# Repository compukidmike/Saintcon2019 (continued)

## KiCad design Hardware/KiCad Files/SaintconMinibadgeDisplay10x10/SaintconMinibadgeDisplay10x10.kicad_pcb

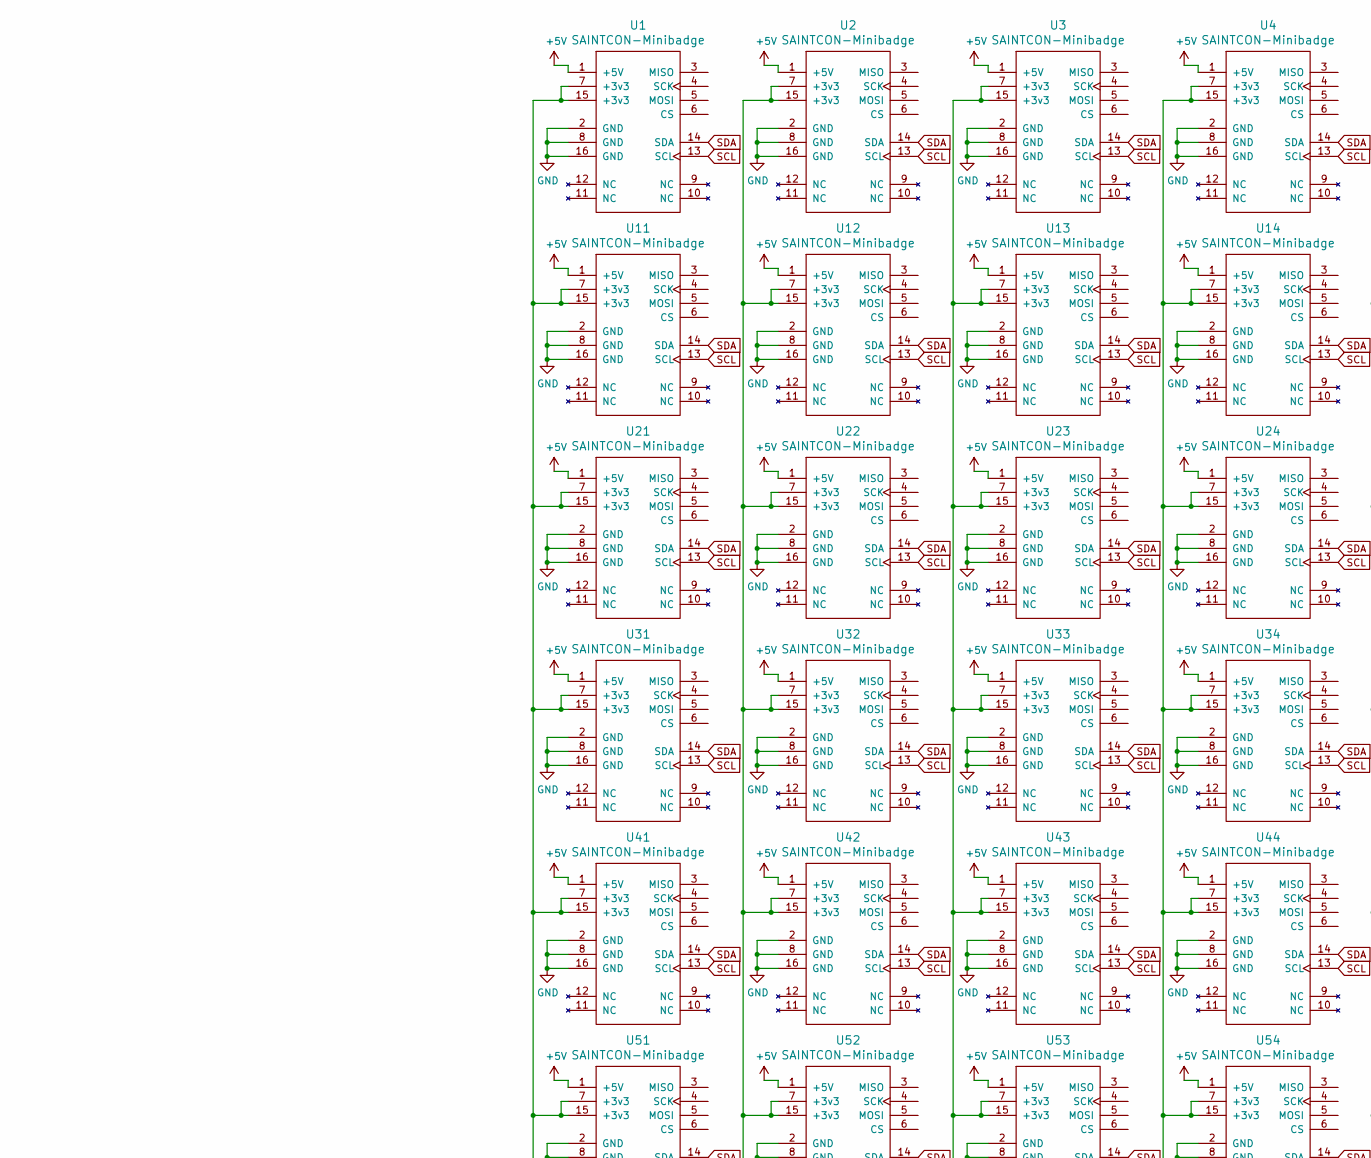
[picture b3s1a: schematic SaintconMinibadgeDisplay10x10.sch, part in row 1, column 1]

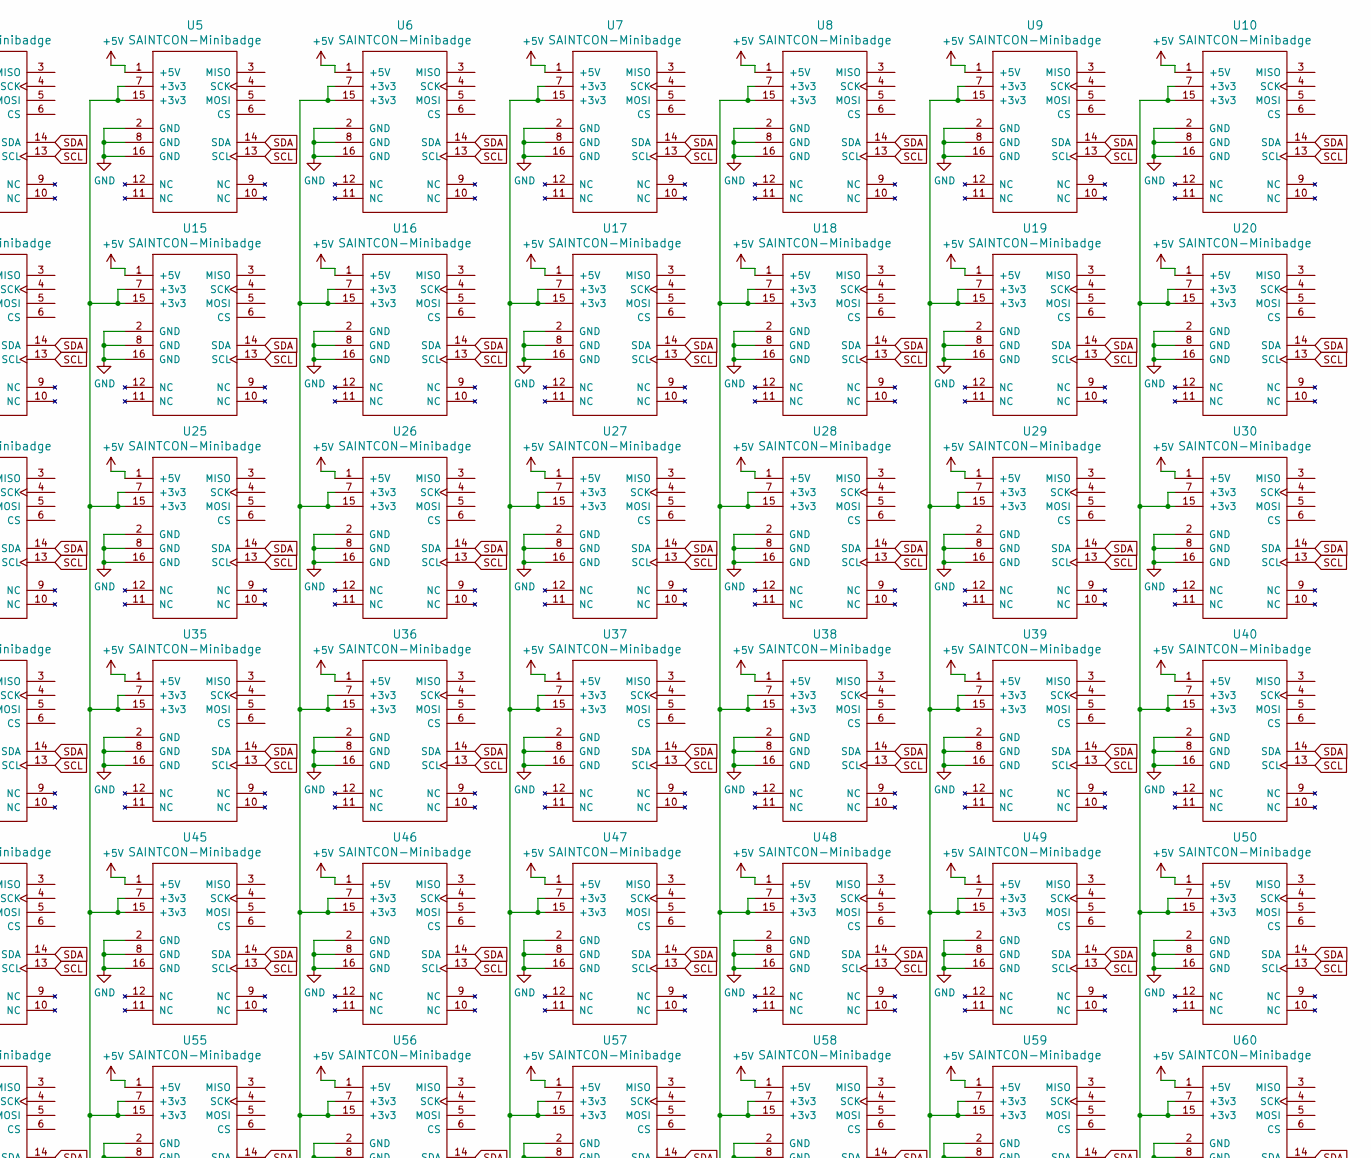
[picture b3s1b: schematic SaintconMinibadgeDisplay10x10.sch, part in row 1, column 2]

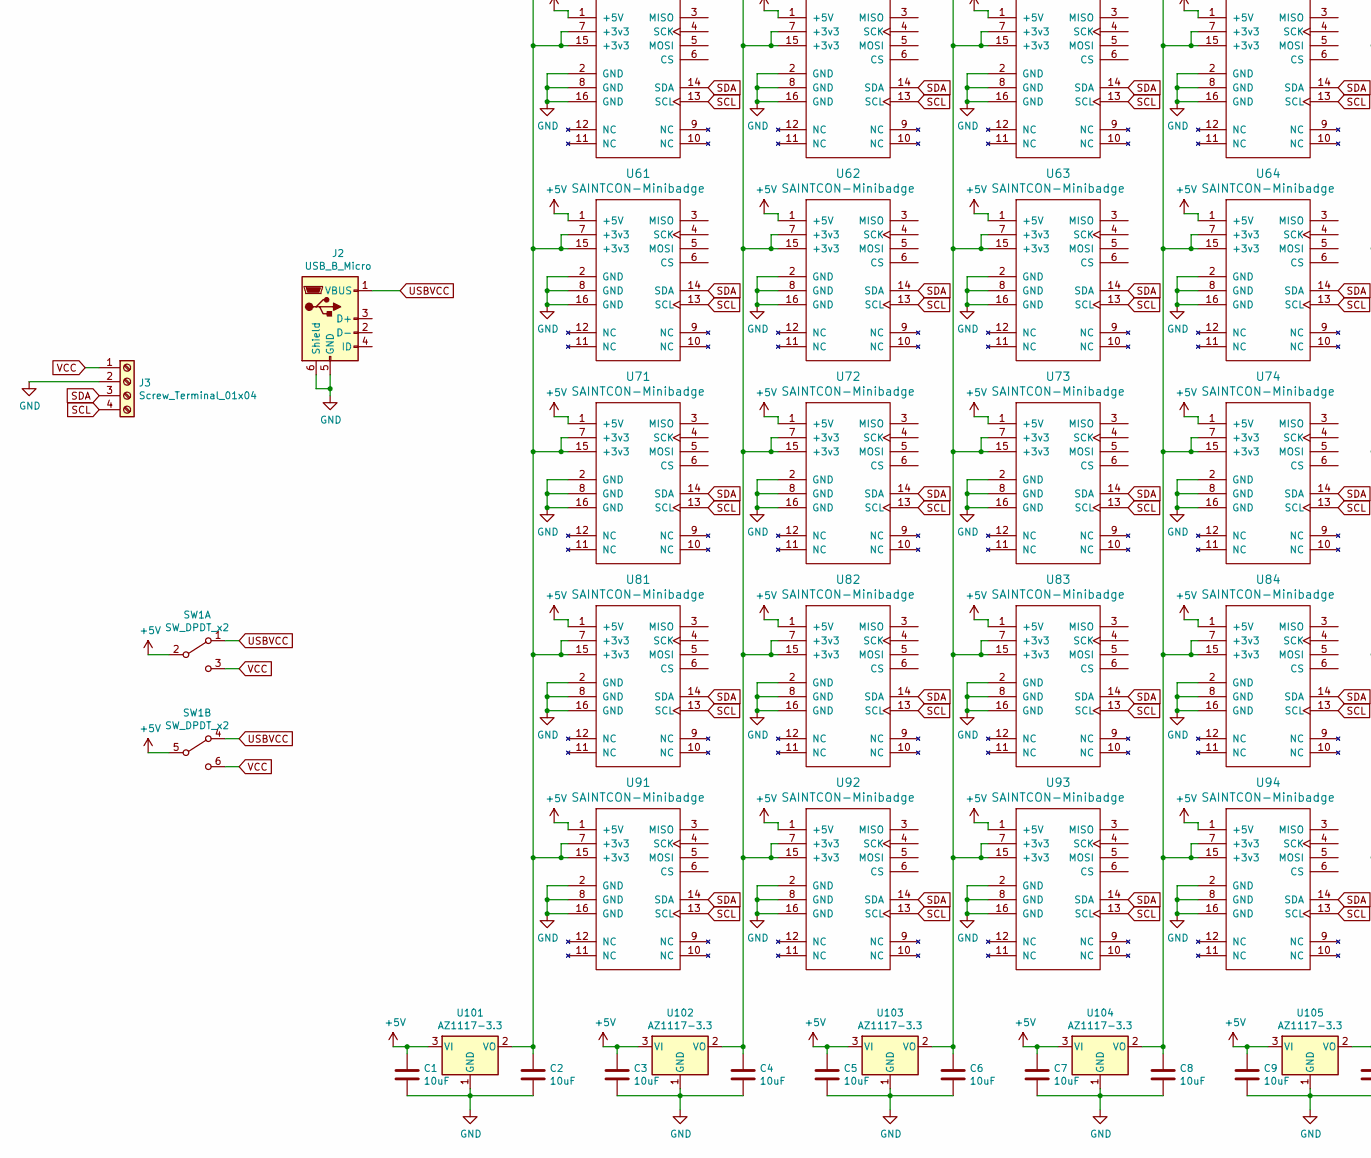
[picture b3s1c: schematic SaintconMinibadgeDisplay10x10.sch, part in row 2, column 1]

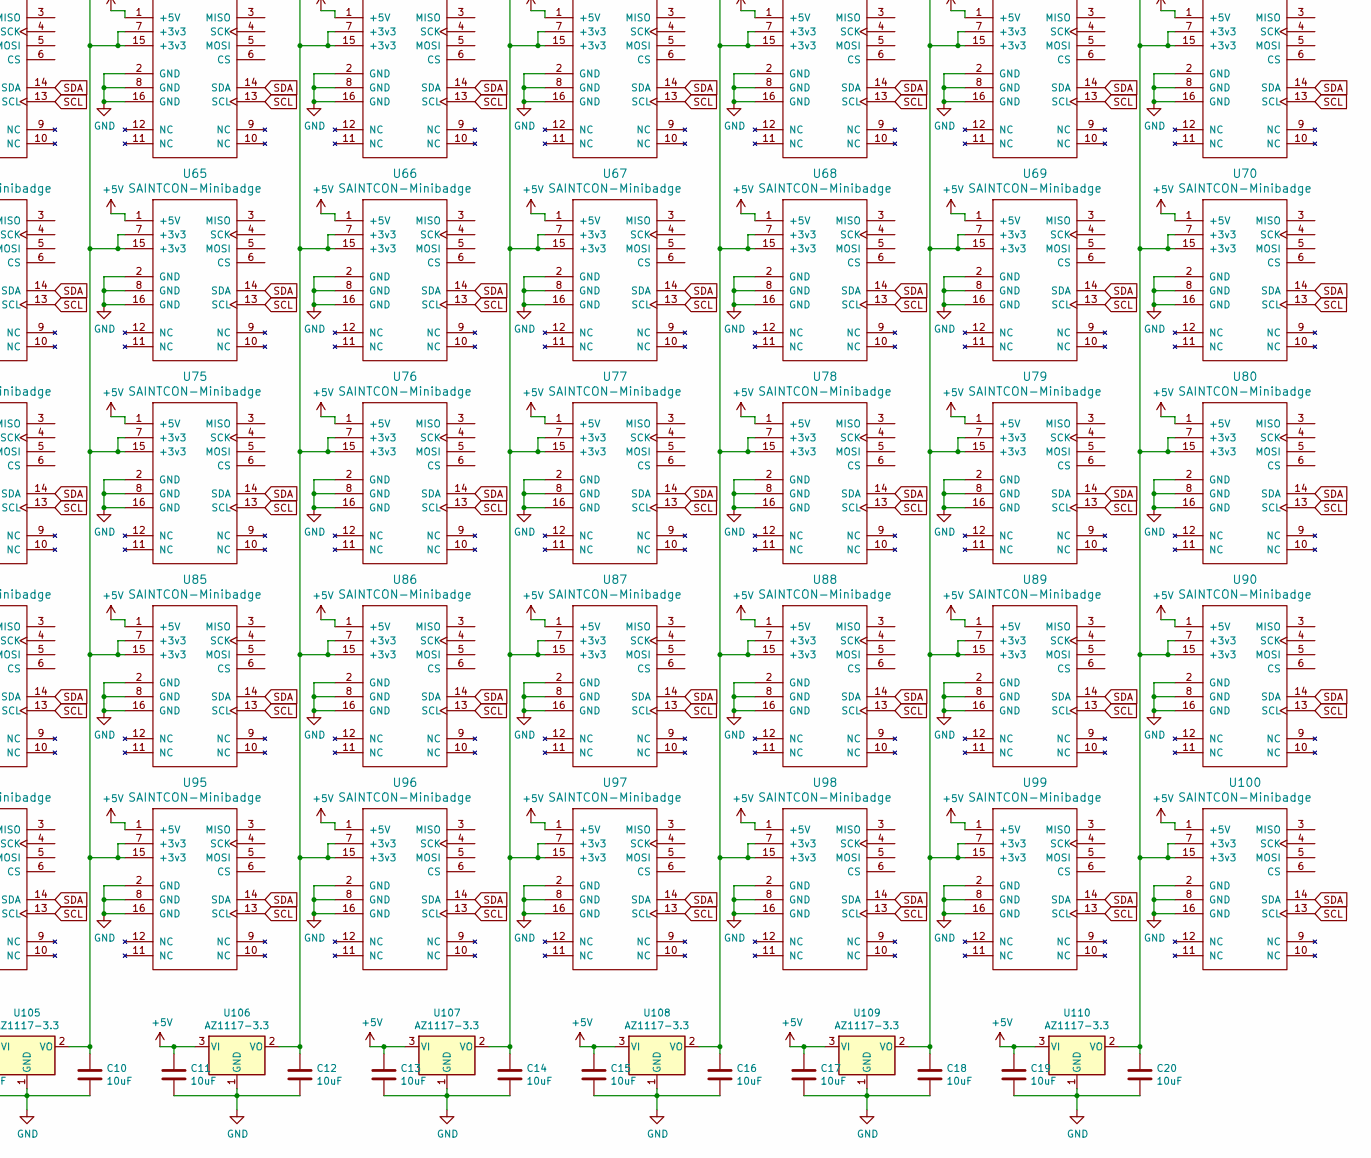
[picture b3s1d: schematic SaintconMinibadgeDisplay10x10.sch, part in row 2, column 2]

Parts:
C1, C2, C3, C4, C5, C6, C7, C8, C9, C10, C11, C12, C13, C14, C15, C16, C17, C18, C19, C20: 10uF; C_0805_HandSoldering
J2: USB_B_Micro; 10118192-0002LF
J3: Screw_Terminal_01x04; SCREWTERMINAL-3.5MM-4
SW1: SW_DPDT_x2; MFS201N-9-Z
U1, U2, U3, U4, U5, U6, U7, U8, U9, U10, U11, U12, U13, U14, U15, U16, U17, U18, U19, U20, U21, U22, U23, U24, U25, U26, U27, U28, U29, U30, U31, U32, U33, U34, U35, U36, U37, U38, U39, U40, U41, U42, U43, U44, U45, U46, U47, U48, U49, U50, U51, U52, U53, U54, U55, U56, U57, U58, U59, U60, U61, U62, U63, U64, U65, U66, U67, U68, U69, U70, U71, U72, U73, U74, U75, U76, U77, U78, U79, U80, U81, U82, U83, U84, U85, U86, U87, U88, U89, U90, U91, U92, U93, U94, U95, U96, U97, U98, U99, U100: SAINTCON-Minibadge; SAINTCON-Minibadge-Shiny
U101, U102, U103, U104, U105, U106, U107, U108, U109, U110: AZ1117-3.3; SOT-223-3_TabPin2

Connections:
+5V: C1.1, C3.1, C5.1, C7.1, C9.1, C11.1, C13.1, C15.1, C17.1, C19.1, SW1.2 (B), SW1.5 (B), U1.1 (+5V), U2.1 (+5V), U3.1 (+5V), U4.1 (+5V), U5.1 (+5V), U6.1 (+5V), U7.1 (+5V), U8.1 (+5V), U9.1 (+5V), U10.1 (+5V), U11.1 (+5V), U12.1 (+5V), U13.1 (+5V), U14.1 (+5V), U15.1 (+5V), U16.1 (+5V), U17.1 (+5V), U18.1 (+5V), U19.1 (+5V), U20.1 (+5V), U21.1 (+5V), U22.1 (+5V), U23.1 (+5V), U24.1 (+5V), U25.1 (+5V), U26.1 (+5V), U27.1 (+5V), U28.1 (+5V), U29.1 (+5V), U30.1 (+5V), U31.1 (+5V), U32.1 (+5V), U33.1 (+5V), U34.1 (+5V), U35.1 (+5V), U36.1 (+5V), U37.1 (+5V), U38.1 (+5V), U39.1 (+5V), U40.1 (+5V), U41.1 (+5V), U42.1 (+5V), U43.1 (+5V), U44.1 (+5V), U45.1 (+5V), U46.1 (+5V), U47.1 (+5V), U48.1 (+5V), U49.1 (+5V), U50.1 (+5V), U51.1 (+5V), U52.1 (+5V), U53.1 (+5V), U54.1 (+5V), U55.1 (+5V), U56.1 (+5V), U57.1 (+5V), U58.1 (+5V), U59.1 (+5V), U60.1 (+5V), U61.1 (+5V), U62.1 (+5V), U63.1 (+5V), U64.1 (+5V), U65.1 (+5V), U66.1 (+5V), U67.1 (+5V), U68.1 (+5V), U69.1 (+5V), U70.1 (+5V), U71.1 (+5V), U72.1 (+5V), U73.1 (+5V), U74.1 (+5V), U75.1 (+5V), U76.1 (+5V), U77.1 (+5V), U78.1 (+5V), U79.1 (+5V), U80.1 (+5V), U81.1 (+5V), U82.1 (+5V), U83.1 (+5V), U84.1 (+5V), U85.1 (+5V), U86.1 (+5V), U87.1 (+5V), U88.1 (+5V), U89.1 (+5V), U90.1 (+5V), U91.1 (+5V), U92.1 (+5V), U93.1 (+5V), U94.1 (+5V), U95.1 (+5V), U96.1 (+5V), U97.1 (+5V), U98.1 (+5V), U99.1 (+5V), U100.1 (+5V), U101.3 (VI), U102.3 (VI), U103.3 (VI), U104.3 (VI), U105.3 (VI), U106.3 (VI), U107.3 (VI), U108.3 (VI), U109.3 (VI), U110.3 (VI)
GND: C1.2, C2.2, C3.2, C4.2, C5.2, C6.2, C7.2, C8.2, C9.2, C10.2, C11.2, C12.2, C13.2, C14.2, C15.2, C16.2, C17.2, C18.2, C19.2, C20.2, J2.5 (GND), J2.6 (Shield), J3.2, U1.2 (GND), U1.8 (GND), U1.16 (GND), U2.2 (GND), U2.8 (GND), U2.16 (GND), U3.2 (GND), U3.8 (GND), U3.16 (GND), U4.2 (GND), U4.8 (GND), U4.16 (GND), U5.2 (GND), U5.8 (GND), U5.16 (GND), U6.2 (GND), U6.8 (GND), U6.16 (GND), U7.2 (GND), U7.8 (GND), U7.16 (GND), U8.2 (GND), U8.8 (GND), U8.16 (GND), U9.2 (GND), U9.8 (GND), U9.16 (GND), U10.2 (GND), U10.8 (GND), U10.16 (GND), U11.2 (GND), U11.8 (GND), U11.16 (GND), U12.2 (GND), U12.8 (GND), U12.16 (GND), U13.2 (GND), U13.8 (GND), U13.16 (GND), U14.2 (GND), U14.8 (GND), U14.16 (GND), U15.2 (GND), U15.8 (GND), U15.16 (GND), U16.2 (GND), U16.8 (GND), U16.16 (GND), U17.2 (GND), U17.8 (GND), U17.16 (GND), U18.2 (GND), U18.8 (GND), U18.16 (GND), U19.2 (GND), U19.8 (GND), U19.16 (GND), U20.2 (GND), U20.8 (GND), U20.16 (GND), U21.2 (GND), U21.8 (GND), U21.16 (GND), U22.2 (GND), U22.8 (GND), U22.16 (GND), U23.2 (GND), U23.8 (GND), U23.16 (GND), U24.2 (GND), U24.8 (GND), U24.16 (GND), U25.2 (GND), U25.8 (GND), U25.16 (GND), U26.2 (GND), U26.8 (GND), U26.16 (GND), U27.2 (GND), U27.8 (GND), U27.16 (GND), U28.2 (GND), U28.8 (GND), U28.16 (GND), U29.2 (GND), U29.8 (GND), U29.16 (GND), U30.2 (GND), U30.8 (GND), U30.16 (GND), U31.2 (GND), U31.8 (GND), U31.16 (GND), U32.2 (GND), U32.8 (GND), U32.16 (GND), U33.2 (GND), U33.8 (GND), U33.16 (GND), U34.2 (GND), U34.8 (GND), U34.16 (GND), U35.2 (GND), U35.8 (GND), U35.16 (GND), U36.2 (GND), U36.8 (GND), U36.16 (GND), U37.2 (GND), U37.8 (GND), U37.16 (GND), U38.2 (GND), U38.8 (GND), U38.16 (GND), U39.2 (GND), U39.8 (GND), U39.16 (GND), U40.2 (GND), U40.8 (GND), U40.16 (GND), U41.2 (GND), U41.8 (GND), U41.16 (GND), U42.2 (GND), U42.8 (GND), U42.16 (GND), U43.2 (GND), U43.8 (GND), U43.16 (GND), U44.2 (GND), U44.8 (GND), U44.16 (GND), U45.2 (GND), U45.8 (GND), U45.16 (GND), U46.2 (GND), U46.8 (GND), U46.16 (GND), U47.2 (GND), U47.8 (GND), U47.16 (GND), U48.2 (GND), U48.8 (GND), U48.16 (GND), U49.2 (GND), U49.8 (GND), U49.16 (GND), U50.2 (GND), U50.8 (GND), U50.16 (GND), U51.2 (GND), U51.8 (GND), U51.16 (GND), U52.2 (GND), U52.8 (GND), U52.16 (GND), U53.2 (GND), U53.8 (GND), U53.16 (GND), U54.2 (GND), U54.8 (GND), U54.16 (GND), U55.2 (GND), U55.8 (GND), U55.16 (GND), U56.2 (GND), U56.8 (GND), U56.16 (GND), U57.2 (GND), U57.8 (GND), U57.16 (GND), U58.2 (GND), U58.8 (GND), U58.16 (GND), U59.2 (GND), U59.8 (GND), U59.16 (GND), U60.2 (GND), U60.8 (GND), U60.16 (GND), U61.2 (GND), U61.8 (GND), U61.16 (GND), U62.2 (GND), U62.8 (GND), U62.16 (GND), U63.2 (GND), U63.8 (GND), U63.16 (GND), U64.2 (GND), U64.8 (GND), U64.16 (GND), U65.2 (GND), U65.8 (GND), U65.16 (GND), U66.2 (GND), U66.8 (GND), U66.16 (GND), U67.2 (GND), U67.8 (GND), U67.16 (GND), U68.2 (GND), U68.8 (GND), U68.16 (GND), U69.2 (GND), U69.8 (GND), U69.16 (GND), U70.2 (GND), U70.8 (GND), U70.16 (GND), U71.2 (GND), U71.8 (GND), U71.16 (GND), U72.2 (GND), U72.8 (GND), U72.16 (GND), U73.2 (GND), U73.8 (GND), U73.16 (GND), U74.2 (GND), U74.8 (GND), U74.16 (GND), U75.2 (GND), U75.8 (GND), U75.16 (GND), U76.2 (GND), U76.8 (GND), U76.16 (GND), U77.2 (GND), U77.8 (GND), U77.16 (GND), U78.2 (GND), U78.8 (GND), U78.16 (GND), U79.2 (GND), U79.8 (GND), U79.16 (GND), U80.2 (GND), U80.8 (GND), U80.16 (GND), U81.2 (GND), U81.8 (GND), U81.16 (GND), U82.2 (GND), U82.8 (GND), U82.16 (GND), U83.2 (GND), U83.8 (GND), U83.16 (GND), U84.2 (GND), U84.8 (GND), U84.16 (GND), U85.2 (GND), U85.8 (GND), U85.16 (GND), U86.2 (GND), U86.8 (GND), U86.16 (GND), U87.2 (GND), U87.8 (GND), U87.16 (GND), U88.2 (GND), U88.8 (GND), U88.16 (GND), U89.2 (GND), U89.8 (GND), U89.16 (GND), U90.2 (GND), U90.8 (GND), U90.16 (GND), U91.2 (GND), U91.8 (GND), U91.16 (GND), U92.2 (GND), U92.8 (GND), U92.16 (GND), U93.2 (GND), U93.8 (GND), U93.16 (GND), U94.2 (GND), U94.8 (GND), U94.16 (GND), U95.2 (GND), U95.8 (GND), U95.16 (GND), U96.2 (GND), U96.8 (GND), U96.16 (GND), U97.2 (GND), U97.8 (GND), U97.16 (GND), U98.2 (GND), U98.8 (GND), U98.16 (GND), U99.2 (GND), U99.8 (GND), U99.16 (GND), U100.2 (GND), U100.8 (GND), U100.16 (GND), U101.1 (GND), U102.1 (GND), U103.1 (GND), U104.1 (GND), U105.1 (GND), U106.1 (GND), U107.1 (GND), U108.1 (GND), U109.1 (GND), U110.1 (GND)
unnamed: C2.1, U1.7 (+3v3), U1.15 (+3v3), U11.7 (+3v3), U11.15 (+3v3), U21.7 (+3v3), U21.15 (+3v3), U31.7 (+3v3), U31.15 (+3v3), U41.7 (+3v3), U41.15 (+3v3), U51.7 (+3v3), U51.15 (+3v3), U61.7 (+3v3), U61.15 (+3v3), U71.7 (+3v3), U71.15 (+3v3), U81.7 (+3v3), U81.15 (+3v3), U91.7 (+3v3), U91.15 (+3v3), U101.2 (VO)
unnamed: C4.1, U2.7 (+3v3), U2.15 (+3v3), U12.7 (+3v3), U12.15 (+3v3), U22.7 (+3v3), U22.15 (+3v3), U32.7 (+3v3), U32.15 (+3v3), U42.7 (+3v3), U42.15 (+3v3), U52.7 (+3v3), U52.15 (+3v3), U62.7 (+3v3), U62.15 (+3v3), U72.7 (+3v3), U72.15 (+3v3), U82.7 (+3v3), U82.15 (+3v3), U92.7 (+3v3), U92.15 (+3v3), U102.2 (VO)
unnamed: C6.1, U3.7 (+3v3), U3.15 (+3v3), U13.7 (+3v3), U13.15 (+3v3), U23.7 (+3v3), U23.15 (+3v3), U33.7 (+3v3), U33.15 (+3v3), U43.7 (+3v3), U43.15 (+3v3), U53.7 (+3v3), U53.15 (+3v3), U63.7 (+3v3), U63.15 (+3v3), U73.7 (+3v3), U73.15 (+3v3), U83.7 (+3v3), U83.15 (+3v3), U93.7 (+3v3), U93.15 (+3v3), U103.2 (VO)
unnamed: C8.1, U4.7 (+3v3), U4.15 (+3v3), U14.7 (+3v3), U14.15 (+3v3), U24.7 (+3v3), U24.15 (+3v3), U34.7 (+3v3), U34.15 (+3v3), U44.7 (+3v3), U44.15 (+3v3), U54.7 (+3v3), U54.15 (+3v3), U64.7 (+3v3), U64.15 (+3v3), U74.7 (+3v3), U74.15 (+3v3), U84.7 (+3v3), U84.15 (+3v3), U94.7 (+3v3), U94.15 (+3v3), U104.2 (VO)
unnamed: C10.1, U5.7 (+3v3), U5.15 (+3v3), U15.7 (+3v3), U15.15 (+3v3), U25.7 (+3v3), U25.15 (+3v3), U35.7 (+3v3), U35.15 (+3v3), U45.7 (+3v3), U45.15 (+3v3), U55.7 (+3v3), U55.15 (+3v3), U65.7 (+3v3), U65.15 (+3v3), U75.7 (+3v3), U75.15 (+3v3), U85.7 (+3v3), U85.15 (+3v3), U95.7 (+3v3), U95.15 (+3v3), U105.2 (VO)
unnamed: C12.1, U6.7 (+3v3), U6.15 (+3v3), U16.7 (+3v3), U16.15 (+3v3), U26.7 (+3v3), U26.15 (+3v3), U36.7 (+3v3), U36.15 (+3v3), U46.7 (+3v3), U46.15 (+3v3), U56.7 (+3v3), U56.15 (+3v3), U66.7 (+3v3), U66.15 (+3v3), U76.7 (+3v3), U76.15 (+3v3), U86.7 (+3v3), U86.15 (+3v3), U96.7 (+3v3), U96.15 (+3v3), U106.2 (VO)
unnamed: C14.1, U7.7 (+3v3), U7.15 (+3v3), U17.7 (+3v3), U17.15 (+3v3), U27.7 (+3v3), U27.15 (+3v3), U37.7 (+3v3), U37.15 (+3v3), U47.7 (+3v3), U47.15 (+3v3), U57.7 (+3v3), U57.15 (+3v3), U67.7 (+3v3), U67.15 (+3v3), U77.7 (+3v3), U77.15 (+3v3), U87.7 (+3v3), U87.15 (+3v3), U97.7 (+3v3), U97.15 (+3v3), U107.2 (VO)
unnamed: C16.1, U8.7 (+3v3), U8.15 (+3v3), U18.7 (+3v3), U18.15 (+3v3), U28.7 (+3v3), U28.15 (+3v3), U38.7 (+3v3), U38.15 (+3v3), U48.7 (+3v3), U48.15 (+3v3), U58.7 (+3v3), U58.15 (+3v3), U68.7 (+3v3), U68.15 (+3v3), U78.7 (+3v3), U78.15 (+3v3), U88.7 (+3v3), U88.15 (+3v3), U98.7 (+3v3), U98.15 (+3v3), U108.2 (VO)
unnamed: C18.1, U9.7 (+3v3), U9.15 (+3v3), U19.7 (+3v3), U19.15 (+3v3), U29.7 (+3v3), U29.15 (+3v3), U39.7 (+3v3), U39.15 (+3v3), U49.7 (+3v3), U49.15 (+3v3), U59.7 (+3v3), U59.15 (+3v3), U69.7 (+3v3), U69.15 (+3v3), U79.7 (+3v3), U79.15 (+3v3), U89.7 (+3v3), U89.15 (+3v3), U99.7 (+3v3), U99.15 (+3v3), U109.2 (VO)
unnamed: C20.1, U10.7 (+3v3), U10.15 (+3v3), U20.7 (+3v3), U20.15 (+3v3), U30.7 (+3v3), U30.15 (+3v3), U40.7 (+3v3), U40.15 (+3v3), U50.7 (+3v3), U50.15 (+3v3), U60.7 (+3v3), U60.15 (+3v3), U70.7 (+3v3), U70.15 (+3v3), U80.7 (+3v3), U80.15 (+3v3), U90.7 (+3v3), U90.15 (+3v3), U100.7 (+3v3), U100.15 (+3v3), U110.2 (VO)
SCL: J3.4, U1.13 (SCL), U2.13 (SCL), U3.13 (SCL), U4.13 (SCL), U5.13 (SCL), U6.13 (SCL), U7.13 (SCL), U8.13 (SCL), U9.13 (SCL), U10.13 (SCL), U11.13 (SCL), U12.13 (SCL), U13.13 (SCL), U14.13 (SCL), U15.13 (SCL), U16.13 (SCL), U17.13 (SCL), U18.13 (SCL), U19.13 (SCL), U20.13 (SCL), U21.13 (SCL), U22.13 (SCL), U23.13 (SCL), U24.13 (SCL), U25.13 (SCL), U26.13 (SCL), U27.13 (SCL), U28.13 (SCL), U29.13 (SCL), U30.13 (SCL), U31.13 (SCL), U32.13 (SCL), U33.13 (SCL), U34.13 (SCL), U35.13 (SCL), U36.13 (SCL), U37.13 (SCL), U38.13 (SCL), U39.13 (SCL), U40.13 (SCL), U41.13 (SCL), U42.13 (SCL), U43.13 (SCL), U44.13 (SCL), U45.13 (SCL), U46.13 (SCL), U47.13 (SCL), U48.13 (SCL), U49.13 (SCL), U50.13 (SCL), U51.13 (SCL), U52.13 (SCL), U53.13 (SCL), U54.13 (SCL), U55.13 (SCL), U56.13 (SCL), U57.13 (SCL), U58.13 (SCL), U59.13 (SCL), U60.13 (SCL), U61.13 (SCL), U62.13 (SCL), U63.13 (SCL), U64.13 (SCL), U65.13 (SCL), U66.13 (SCL), U67.13 (SCL), U68.13 (SCL), U69.13 (SCL), U70.13 (SCL), U71.13 (SCL), U72.13 (SCL), U73.13 (SCL), U74.13 (SCL), U75.13 (SCL), U76.13 (SCL), U77.13 (SCL), U78.13 (SCL), U79.13 (SCL), U80.13 (SCL), U81.13 (SCL), U82.13 (SCL), U83.13 (SCL), U84.13 (SCL), U85.13 (SCL), U86.13 (SCL), U87.13 (SCL), U88.13 (SCL), U89.13 (SCL), U90.13 (SCL), U91.13 (SCL), U92.13 (SCL), U93.13 (SCL), U94.13 (SCL), U95.13 (SCL), U96.13 (SCL), U97.13 (SCL), U98.13 (SCL), U99.13 (SCL), U100.13 (SCL)
SDA: J3.3, U1.14 (SDA), U2.14 (SDA), U3.14 (SDA), U4.14 (SDA), U5.14 (SDA), U6.14 (SDA), U7.14 (SDA), U8.14 (SDA), U9.14 (SDA), U10.14 (SDA), U11.14 (SDA), U12.14 (SDA), U13.14 (SDA), U14.14 (SDA), U15.14 (SDA), U16.14 (SDA), U17.14 (SDA), U18.14 (SDA), U19.14 (SDA), U20.14 (SDA), U21.14 (SDA), U22.14 (SDA), U23.14 (SDA), U24.14 (SDA), U25.14 (SDA), U26.14 (SDA), U27.14 (SDA), U28.14 (SDA), U29.14 (SDA), U30.14 (SDA), U31.14 (SDA), U32.14 (SDA), U33.14 (SDA), U34.14 (SDA), U35.14 (SDA), U36.14 (SDA), U37.14 (SDA), U38.14 (SDA), U39.14 (SDA), U40.14 (SDA), U41.14 (SDA), U42.14 (SDA), U43.14 (SDA), U44.14 (SDA), U45.14 (SDA), U46.14 (SDA), U47.14 (SDA), U48.14 (SDA), U49.14 (SDA), U50.14 (SDA), U51.14 (SDA), U52.14 (SDA), U53.14 (SDA), U54.14 (SDA), U55.14 (SDA), U56.14 (SDA), U57.14 (SDA), U58.14 (SDA), U59.14 (SDA), U60.14 (SDA), U61.14 (SDA), U62.14 (SDA), U63.14 (SDA), U64.14 (SDA), U65.14 (SDA), U66.14 (SDA), U67.14 (SDA), U68.14 (SDA), U69.14 (SDA), U70.14 (SDA), U71.14 (SDA), U72.14 (SDA), U73.14 (SDA), U74.14 (SDA), U75.14 (SDA), U76.14 (SDA), U77.14 (SDA), U78.14 (SDA), U79.14 (SDA), U80.14 (SDA), U81.14 (SDA), U82.14 (SDA), U83.14 (SDA), U84.14 (SDA), U85.14 (SDA), U86.14 (SDA), U87.14 (SDA), U88.14 (SDA), U89.14 (SDA), U90.14 (SDA), U91.14 (SDA), U92.14 (SDA), U93.14 (SDA), U94.14 (SDA), U95.14 (SDA), U96.14 (SDA), U97.14 (SDA), U98.14 (SDA), U99.14 (SDA), U100.14 (SDA)
USBVCC: J2.1 (VBUS), SW1.1 (A), SW1.4 (A)
VCC: J3.1, SW1.3 (C), SW1.6 (C)

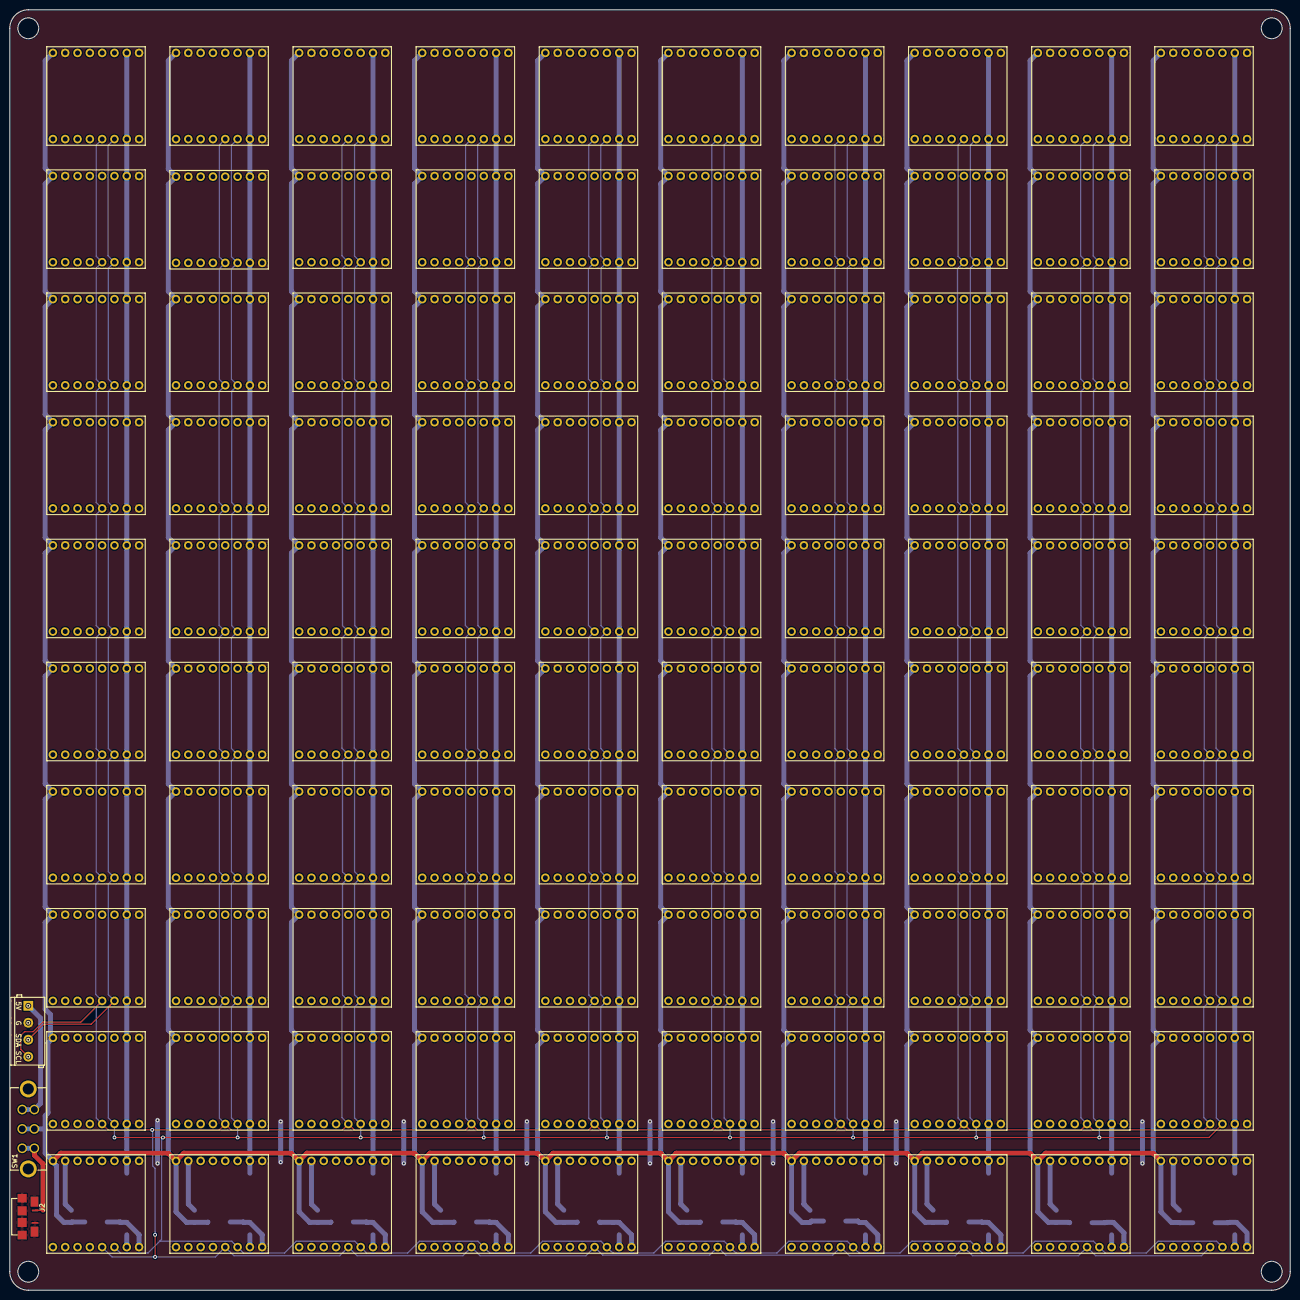
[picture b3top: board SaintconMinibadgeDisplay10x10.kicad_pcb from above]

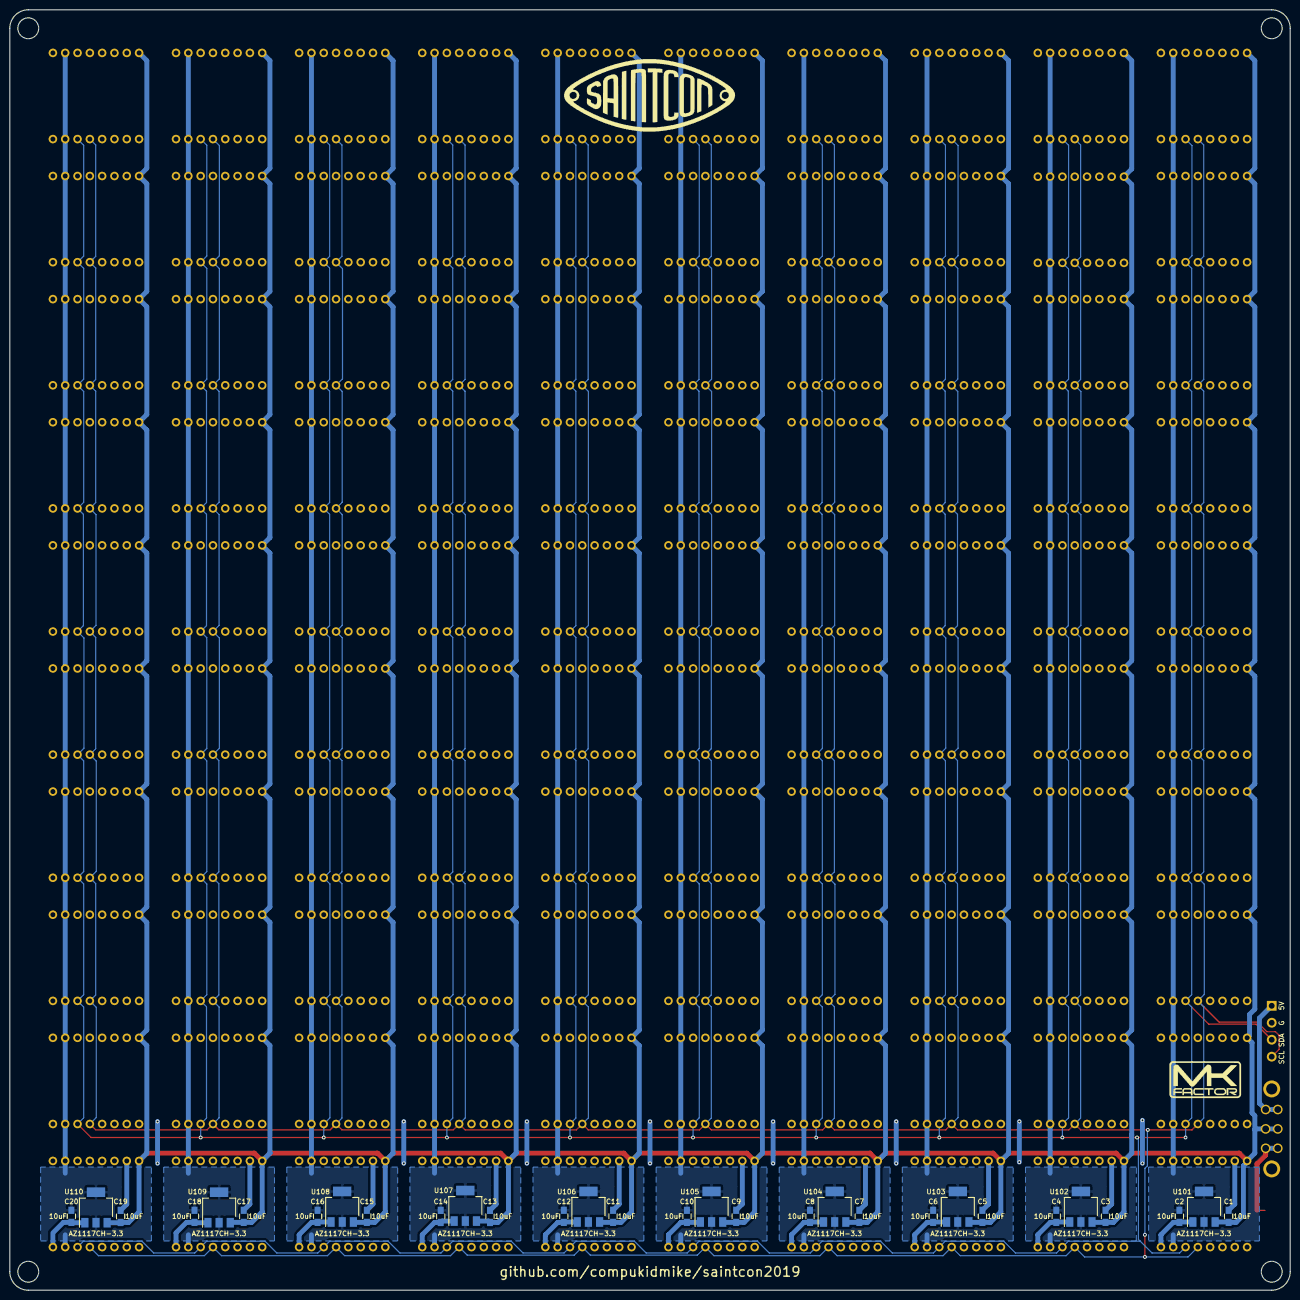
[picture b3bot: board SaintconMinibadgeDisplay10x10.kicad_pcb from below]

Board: 2 copper layers, 264.2 x 264.2 mm, 134 parts (31 on the bottom side), 16 nets.

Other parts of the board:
Ref**: Val**; drawing

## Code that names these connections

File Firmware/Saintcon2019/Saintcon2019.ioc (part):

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Mcu.Name=STM32L433VCTx
Mcu.Package=LQFP100
Mcu.UserName=STM32L433VCTx
PA0.GPIOParameters=PinState,GPIO_PuPd,GPIO_Label,GPIO_ModeDefaultOutputPP
PA0.GPIO_Label=PlugA
PA0.GPIO_ModeDefaultOutputPP=GPIO_MODE_OUTPUT_OD
PA0.GPIO_PuPd=GPIO_PULLUP
PA0.PinState=GPIO_PIN_SET
PA0.Signal=GPIO_Output
PA1.GPIOParameters=PinState,GPIO_PuPd,GPIO_Label,GPIO_ModeDefaultOutputPP
PA1.GPIO_Label=PlugB
PA1.GPIO_ModeDefaultOutputPP=GPIO_MODE_OUTPUT_OD
PA1.GPIO_PuPd=GPIO_PULLUP
PA1.PinState=GPIO_PIN_SET
PA1.Signal=GPIO_Output
PA10.Mode=Asynchronous
PA10.Signal=USART1_RX
PA11.Mode=Device
PA11.Signal=USB_DM
PA12.Mode=Device
PA12.Signal=USB_DP
PA13\ (JTMS-SWDIO).Mode=Serial_Wire
PA13\ (JTMS-SWDIO).Signal=SYS_JTMS-SWDIO
PA14\ (JTCK-SWCLK).Mode=Serial_Wire
PA14\ (JTCK-SWCLK).Signal=SYS_JTCK-SWCLK
PA15\ (JTDI).Mode=NSS_Signal_Hard_Output
PA15\ (JTDI).Signal=SPI1_NSS
PA2.Mode=Asynchronous
PA2.Signal=USART2_TX
PA3.Mode=Asynchronous
PA3.Signal=USART2_RX
PA4.GPIOParameters=PinState,GPIO_PuPd,GPIO_Label,GPIO_ModeDefaultOutputPP
PA4.GPIO_Label=PlugC
PA4.GPIO_ModeDefaultOutputPP=GPIO_MODE_OUTPUT_OD
PA4.GPIO_PuPd=GPIO_PULLUP
PA4.PinState=GPIO_PIN_SET
PA4.Signal=GPIO_Output
PA5.GPIOParameters=PinState,GPIO_PuPd,GPIO_Label,GPIO_ModeDefaultOutputPP
PA5.GPIO_Label=PlugD
PA5.GPIO_ModeDefaultOutputPP=GPIO_MODE_OUTPUT_OD
PA5.GPIO_PuPd=GPIO_PULLUP
PA5.PinState=GPIO_PIN_SET
PA5.Signal=GPIO_Output
PA6.GPIOParameters=PinState,GPIO_PuPd,GPIO_Label,GPIO_ModeDefaultOutputPP
PA6.GPIO_Label=PlugE
PA6.GPIO_ModeDefaultOutputPP=GPIO_MODE_OUTPUT_OD
PA6.GPIO_PuPd=GPIO_PULLUP
PA6.PinState=GPIO_PIN_SET
PA6.Signal=GPIO_Output
PA7.GPIOParameters=GPIO_Speed,PinState,GPIO_PuPd,GPIO_Label,GPIO_ModeDefaultOutputPP
PA7.GPIO_Label=PlugF
PA7.GPIO_ModeDefaultOutputPP=GPIO_MODE_OUTPUT_OD
PA7.GPIO_PuPd=GPIO_PULLUP
PA7.GPIO_Speed=GPIO_SPEED_FREQ_LOW
PA7.PinState=GPIO_PIN_SET
PA7.Signal=GPIO_Output
PA8.GPIOParameters=GPIO_Speed,PinState,GPIO_PuPd,GPIO_Label,GPIO_ModeDefaultOutputPP
PA8.GPIO_Label=PlugG
PA8.GPIO_ModeDefaultOutputPP=GPIO_MODE_OUTPUT_OD
PA8.GPIO_PuPd=GPIO_PULLUP
PA8.GPIO_Speed=GPIO_SPEED_FREQ_LOW
PA8.PinState=GPIO_PIN_SET
PA8.Signal=GPIO_Output
PA9.Mode=Asynchronous
PA9.Signal=USART1_TX
PB0.GPIOParameters=GPIO_Speed,PinState,GPIO_PuPd,GPIO_Label,GPIO_ModeDefaultOutputPP
PB0.GPIO_Label=PlugH
PB0.GPIO_ModeDefaultOutputPP=GPIO_MODE_OUTPUT_OD
PB0.GPIO_PuPd=GPIO_PULLUP
PB0.GPIO_Speed=GPIO_SPEED_FREQ_LOW
PB0.PinState=GPIO_PIN_SET
PB0.Signal=GPIO_Output
PB1.GPIOParameters=GPIO_Speed,PinState,GPIO_PuPd,GPIO_Label,GPIO_ModeDefaultOutputPP
PB1.GPIO_Label=PlugI
PB1.GPIO_ModeDefaultOutputPP=GPIO_MODE_OUTPUT_OD
PB1.GPIO_PuPd=GPIO_PULLUP
PB1.GPIO_Speed=GPIO_SPEED_FREQ_LOW
PB1.PinState=GPIO_PIN_SET
PB1.Signal=GPIO_Output
PB10.Mode=I2C
PB10.Signal=I2C2_SCL
PB11.Mode=I2C
PB11.Signal=I2C2_SDA
PB12.GPIOParameters=GPIO_Label
PB12.GPIO_Label=MB_CS1
PB12.Signal=GPIO_Output
PB13.Mode=Full_Duplex_Master
PB13.Signal=SPI2_SCK
PB14.Mode=Full_Duplex_Master
PB14.Signal=SPI2_MISO
PB15.Mode=Full_Duplex_Master
PB15.Signal=SPI2_MOSI
PB2.GPIOParameters=GPIO_Speed,PinState,GPIO_PuPd,GPIO_Label,GPIO_ModeDefaultOutputPP
PB2.GPIO_Label=PlugJ
PB2.GPIO_ModeDefaultOutputPP=GPIO_MODE_OUTPUT_OD
PB2.GPIO_PuPd=GPIO_PULLUP
PB2.GPIO_Speed=GPIO_SPEED_FREQ_LOW
PB2.PinState=GPIO_PIN_SET
PB2.Signal=GPIO_Output
PB3\ (JTDO-TRACESWO).Mode=Full_Duplex_Master
PB3\ (JTDO-TRACESWO).Signal=SPI1_SCK
PB4\ (NJTRST).Mode=Full_Duplex_Master
PB4\ (NJTRST).Signal=SPI1_MISO
PB5.Mode=Full_Duplex_Master
PB5.Signal=SPI1_MOSI
PB6.GPIOParameters=GPIO_Label
PB6.GPIO_Label=ICE_CRESET
PB6.Signal=GPIO_Output
PB7.GPIOParameters=GPIO_Label
PB7.GPIO_Label=ICE_CDONE
PB7.Signal=GPIO_Input
PB8.Mode=I2C
PB8.Signal=I2C1_SCL
PB9.Mode=I2C
PB9.Signal=I2C1_SDA
PC0.GPIOParameters=GPIO_Speed,PinState,GPIO_PuPd,GPIO_Label,GPIO_ModeDefaultOutputPP
PC0.GPIO_Label=PlugK
PC0.GPIO_ModeDefaultOutputPP=GPIO_MODE_OUTPUT_OD
PC0.GPIO_PuPd=GPIO_PULLUP
PC0.GPIO_Speed=GPIO_SPEED_FREQ_LOW
PC0.PinState=GPIO_PIN_SET
PC0.Signal=GPIO_Output
PC1.GPIOParameters=GPIO_Speed,PinState,GPIO_PuPd,GPIO_Label,GPIO_ModeDefaultOutputPP
PC1.GPIO_Label=PlugL
PC1.GPIO_ModeDefaultOutputPP=GPIO_MODE_OUTPUT_OD
PC1.GPIO_PuPd=GPIO_PULLUP
PC1.GPIO_Speed=GPIO_SPEED_FREQ_LOW
PC1.PinState=GPIO_PIN_SET
PC1.Signal=GPIO_Output
PC10.GPIOParameters=GPIO_Speed,PinState,GPIO_PuPd,GPIO_Label,GPIO_ModeDefaultOutputPP
PC10.GPIO_Label=PlugU
PC10.GPIO_ModeDefaultOutputPP=GPIO_MODE_OUTPUT_OD
PC10.GPIO_PuPd=GPIO_PULLUP
PC10.GPIO_Speed=GPIO_SPEED_FREQ_LOW
PC10.PinState=GPIO_PIN_SET
PC10.Signal=GPIO_Output
PC11.GPIOParameters=GPIO_Speed,PinState,GPIO_PuPd,GPIO_Label,GPIO_ModeDefaultOutputPP
PC11.GPIO_Label=PlugV
PC11.GPIO_ModeDefaultOutputPP=GPIO_MODE_OUTPUT_OD
PC11.GPIO_PuPd=GPIO_PULLUP
PC11.GPIO_Speed=GPIO_SPEED_FREQ_LOW
PC11.PinState=GPIO_PIN_SET
PC11.Signal=GPIO_Output
PC12.GPIOParameters=GPIO_Speed,PinState,GPIO_PuPd,GPIO_Label,GPIO_ModeDefaultOutputPP
PC12.GPIO_Label=PlugW
PC12.GPIO_ModeDefaultOutputPP=GPIO_MODE_OUTPUT_OD
PC12.GPIO_PuPd=GPIO_PULLUP
PC12.GPIO_Speed=GPIO_SPEED_FREQ_LOW
PC12.PinState=GPIO_PIN_SET
PC12.Signal=GPIO_Output
PC13.GPIOParameters=GPIO_Speed,PinState,GPIO_PuPd,GPIO_Label,GPIO_ModeDefaultOutputPP
PC13.GPIO_Label=PlugX
PC13.GPIO_ModeDefaultOutputPP=GPIO_MODE_OUTPUT_OD
PC13.GPIO_PuPd=GPIO_PULLUP
PC13.GPIO_Speed=GPIO_SPEED_FREQ_LOW
PC13.PinState=GPIO_PIN_SET
PC13.Signal=GPIO_Output
PC14-OSC32_IN\ (PC14).GPIOParameters=GPIO_Speed,PinState,GPIO_PuPd,GPIO_Label,GPIO_ModeDefaultOutputPP
PC14-OSC32_IN\ (PC14).GPIO_Label=PlugY
PC14-OSC32_IN\ (PC14).GPIO_ModeDefaultOutputPP=GPIO_MODE_OUTPUT_OD
PC14-OSC32_IN\ (PC14).GPIO_PuPd=GPIO_PULLUP
PC14-OSC32_IN\ (PC14).GPIO_Speed=GPIO_SPEED_FREQ_LOW
PC14-OSC32_IN\ (PC14).PinState=GPIO_PIN_SET
PC14-OSC32_IN\ (PC14).Signal=GPIO_Output
PC15-OSC32_OUT\ (PC15).GPIOParameters=GPIO_Speed,PinState,GPIO_PuPd,GPIO_Label,GPIO_ModeDefaultOutputPP
PC15-OSC32_OUT\ (PC15).GPIO_Label=PlugZ
PC15-OSC32_OUT\ (PC15).GPIO_ModeDefaultOutputPP=GPIO_MODE_OUTPUT_OD
PC15-OSC32_OUT\ (PC15).GPIO_PuPd=GPIO_PULLUP
PC15-OSC32_OUT\ (PC15).GPIO_Speed=GPIO_SPEED_FREQ_LOW
PC15-OSC32_OUT\ (PC15).PinState=GPIO_PIN_SET
PC15-OSC32_OUT\ (PC15).Signal=GPIO_Output
PC2.GPIOParameters=GPIO_Speed,PinState,GPIO_PuPd,GPIO_Label,GPIO_ModeDefaultOutputPP
PC2.GPIO_Label=PlugM
PC2.GPIO_ModeDefaultOutputPP=GPIO_MODE_OUTPUT_OD
PC2.GPIO_PuPd=GPIO_PULLUP
PC2.GPIO_Speed=GPIO_SPEED_FREQ_LOW
PC2.PinState=GPIO_PIN_SET
PC2.Signal=GPIO_Output
PC3.GPIOParameters=GPIO_Speed,PinState,GPIO_PuPd,GPIO_Label,GPIO_ModeDefaultOutputPP
PC3.GPIO_Label=PlugN
PC3.GPIO_ModeDefaultOutputPP=GPIO_MODE_OUTPUT_OD
PC3.GPIO_PuPd=GPIO_PULLUP
PC3.GPIO_Speed=GPIO_SPEED_FREQ_LOW
PC3.PinState=GPIO_PIN_SET
PC3.Signal=GPIO_Output
PC4.GPIOParameters=GPIO_Speed,PinState,GPIO_PuPd,GPIO_Label,GPIO_ModeDefaultOutputPP
PC4.GPIO_Label=PlugO
PC4.GPIO_ModeDefaultOutputPP=GPIO_MODE_OUTPUT_OD
PC4.GPIO_PuPd=GPIO_PULLUP
PC4.GPIO_Speed=GPIO_SPEED_FREQ_LOW
PC4.PinState=GPIO_PIN_SET
PC4.Signal=GPIO_Output
PC5.GPIOParameters=GPIO_Speed,PinState,GPIO_PuPd,GPIO_Label,GPIO_ModeDefaultOutputPP
PC5.GPIO_Label=PlugP
PC5.GPIO_ModeDefaultOutputPP=GPIO_MODE_OUTPUT_OD
PC5.GPIO_PuPd=GPIO_PULLUP
PC5.GPIO_Speed=GPIO_SPEED_FREQ_LOW
PC5.PinState=GPIO_PIN_SET
PC5.Signal=GPIO_Output
PC6.GPIOParameters=GPIO_Speed,PinState,GPIO_PuPd,GPIO_Label,GPIO_ModeDefaultOutputPP
PC6.GPIO_Label=PlugQ
PC6.GPIO_ModeDefaultOutputPP=GPIO_MODE_OUTPUT_OD
PC6.GPIO_PuPd=GPIO_PULLUP
PC6.GPIO_Speed=GPIO_SPEED_FREQ_LOW
PC6.PinState=GPIO_PIN_SET
PC6.Signal=GPIO_Output
PC7.GPIOParameters=GPIO_Speed,PinState,GPIO_PuPd,GPIO_Label,GPIO_ModeDefaultOutputPP
PC7.GPIO_Label=PlugR
PC7.GPIO_ModeDefaultOutputPP=GPIO_MODE_OUTPUT_OD
PC7.GPIO_PuPd=GPIO_PULLUP
PC7.GPIO_Speed=GPIO_SPEED_FREQ_LOW
PC7.PinState=GPIO_PIN_SET
PC7.Signal=GPIO_Output
PC8.GPIOParameters=GPIO_Speed,PinState,GPIO_PuPd,GPIO_Label,GPIO_ModeDefaultOutputPP
PC8.GPIO_Label=PlugS
PC8.GPIO_ModeDefaultOutputPP=GPIO_MODE_OUTPUT_OD
PC8.GPIO_PuPd=GPIO_PULLUP
PC8.GPIO_Speed=GPIO_SPEED_FREQ_LOW
PC8.PinState=GPIO_PIN_SET
PC8.Signal=GPIO_Output
PC9.GPIOParameters=GPIO_Speed,PinState,GPIO_PuPd,GPIO_Label,GPIO_ModeDefaultOutputPP
PC9.GPIO_Label=PlugT
PC9.GPIO_ModeDefaultOutputPP=GPIO_MODE_OUTPUT_OD
PC9.GPIO_PuPd=GPIO_PULLUP
PC9.GPIO_Speed=GPIO_SPEED_FREQ_LOW
PC9.PinState=GPIO_PIN_SET
PC9.Signal=GPIO_Output
PD0.GPIOParameters=GPIO_PuPd,GPIO_Label
PD0.GPIO_Label=KBD_O
PD0.GPIO_PuPd=GPIO_PULLUP
PD0.Signal=GPIO_Input
PD1.GPIOParameters=GPIO_PuPd,GPIO_Label
PD1.GPIO_Label=KBD_P
PD1.GPIO_PuPd=GPIO_PULLUP
PD1.Signal=GPIO_Input
PD10.GPIOParameters=GPIO_PuPd,GPIO_Label
PD10.GPIO_Label=KBD_X
PD10.GPIO_PuPd=GPIO_PULLUP
PD10.Signal=GPIO_Input
PD11.GPIOParameters=GPIO_PuPd,GPIO_Label
PD11.GPIO_Label=KBD_Y
PD11.GPIO_PuPd=GPIO_PULLUP
PD11.Signal=GPIO_Input
PD12.GPIOParameters=GPIO_PuPd,GPIO_Label
PD12.GPIO_Label=KBD_Z
PD12.GPIO_PuPd=GPIO_PULLUP
PD12.Signal=GPIO_Input
PD13.GPIOParameters=GPIO_Label
PD13.GPIO_Label=MB_CS2
PD13.Signal=GPIO_Output
PD14.GPIOParameters=GPIO_Label
PD14.GPIO_Label=MB_CS3
PD14.Signal=GPIO_Output
PD15.GPIOParameters=GPIO_PuPd,GPIO_Label,GPIO_ModeDefaultEXTI

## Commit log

2019-10-22 Init
2019-10-22 add badge build instructions
2019-10-22 badge instructions
2019-10-28 Add Firmware
2019-10-28 add hardware files
2019-10-28 added FPGA files
2019-10-28 add pdf of schematic
2019-10-28 add pdf schematics
2020-01-25 New Firmware
    New firmware to allow badge challenge completion at home
